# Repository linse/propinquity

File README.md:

Propinquity
===========

Propinquity is a full-body game that is a hybrid between fighting and dancing games. Two players wear proximity sensors on different body parts and as they move to the music, different sensors patches on their bodies light up to indicate when they are active. The players attempt to get as close as possible to active patches on the other player’s body to score points. The longer s(he) can stay “in the sweet spot” (but without actually touching), the higher the resulting score.

[Propinquity on the TAG website](http://playpr.hexagram.ca/projects/?proj=2)

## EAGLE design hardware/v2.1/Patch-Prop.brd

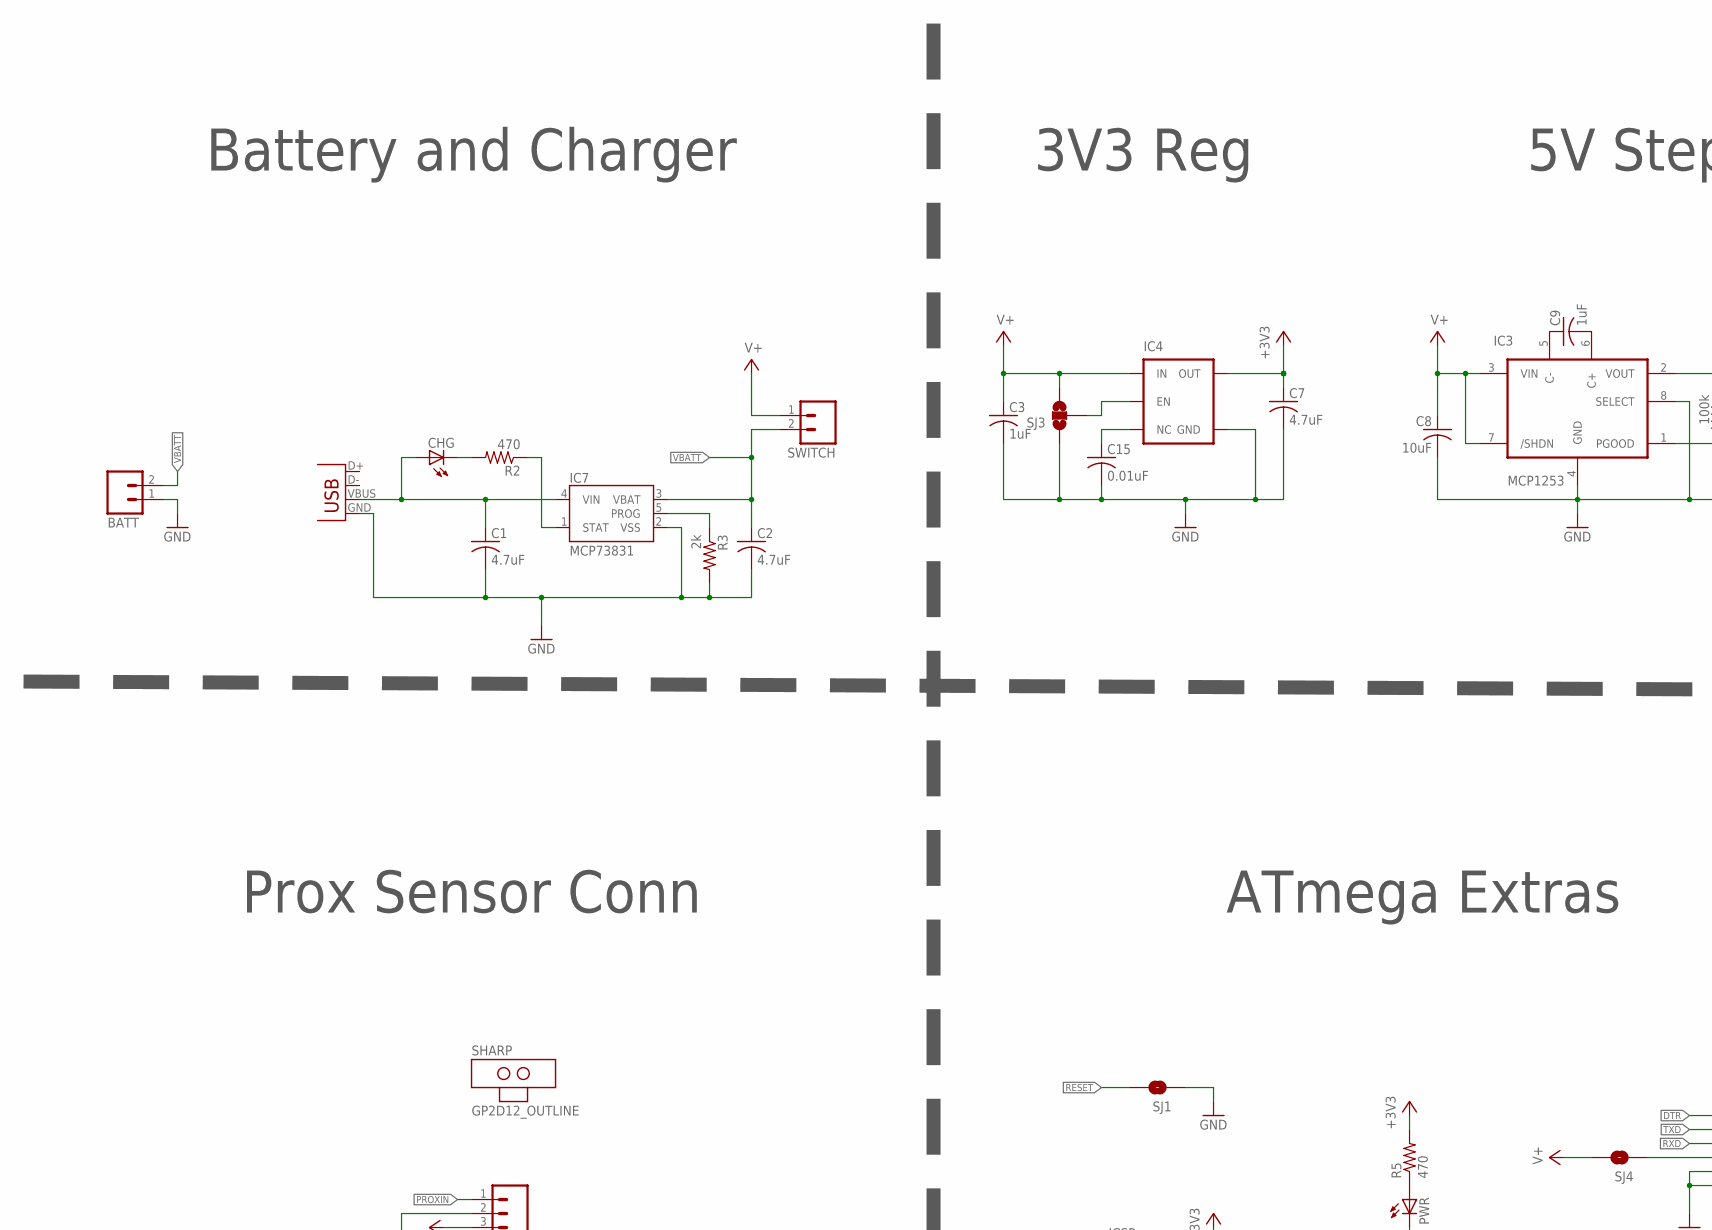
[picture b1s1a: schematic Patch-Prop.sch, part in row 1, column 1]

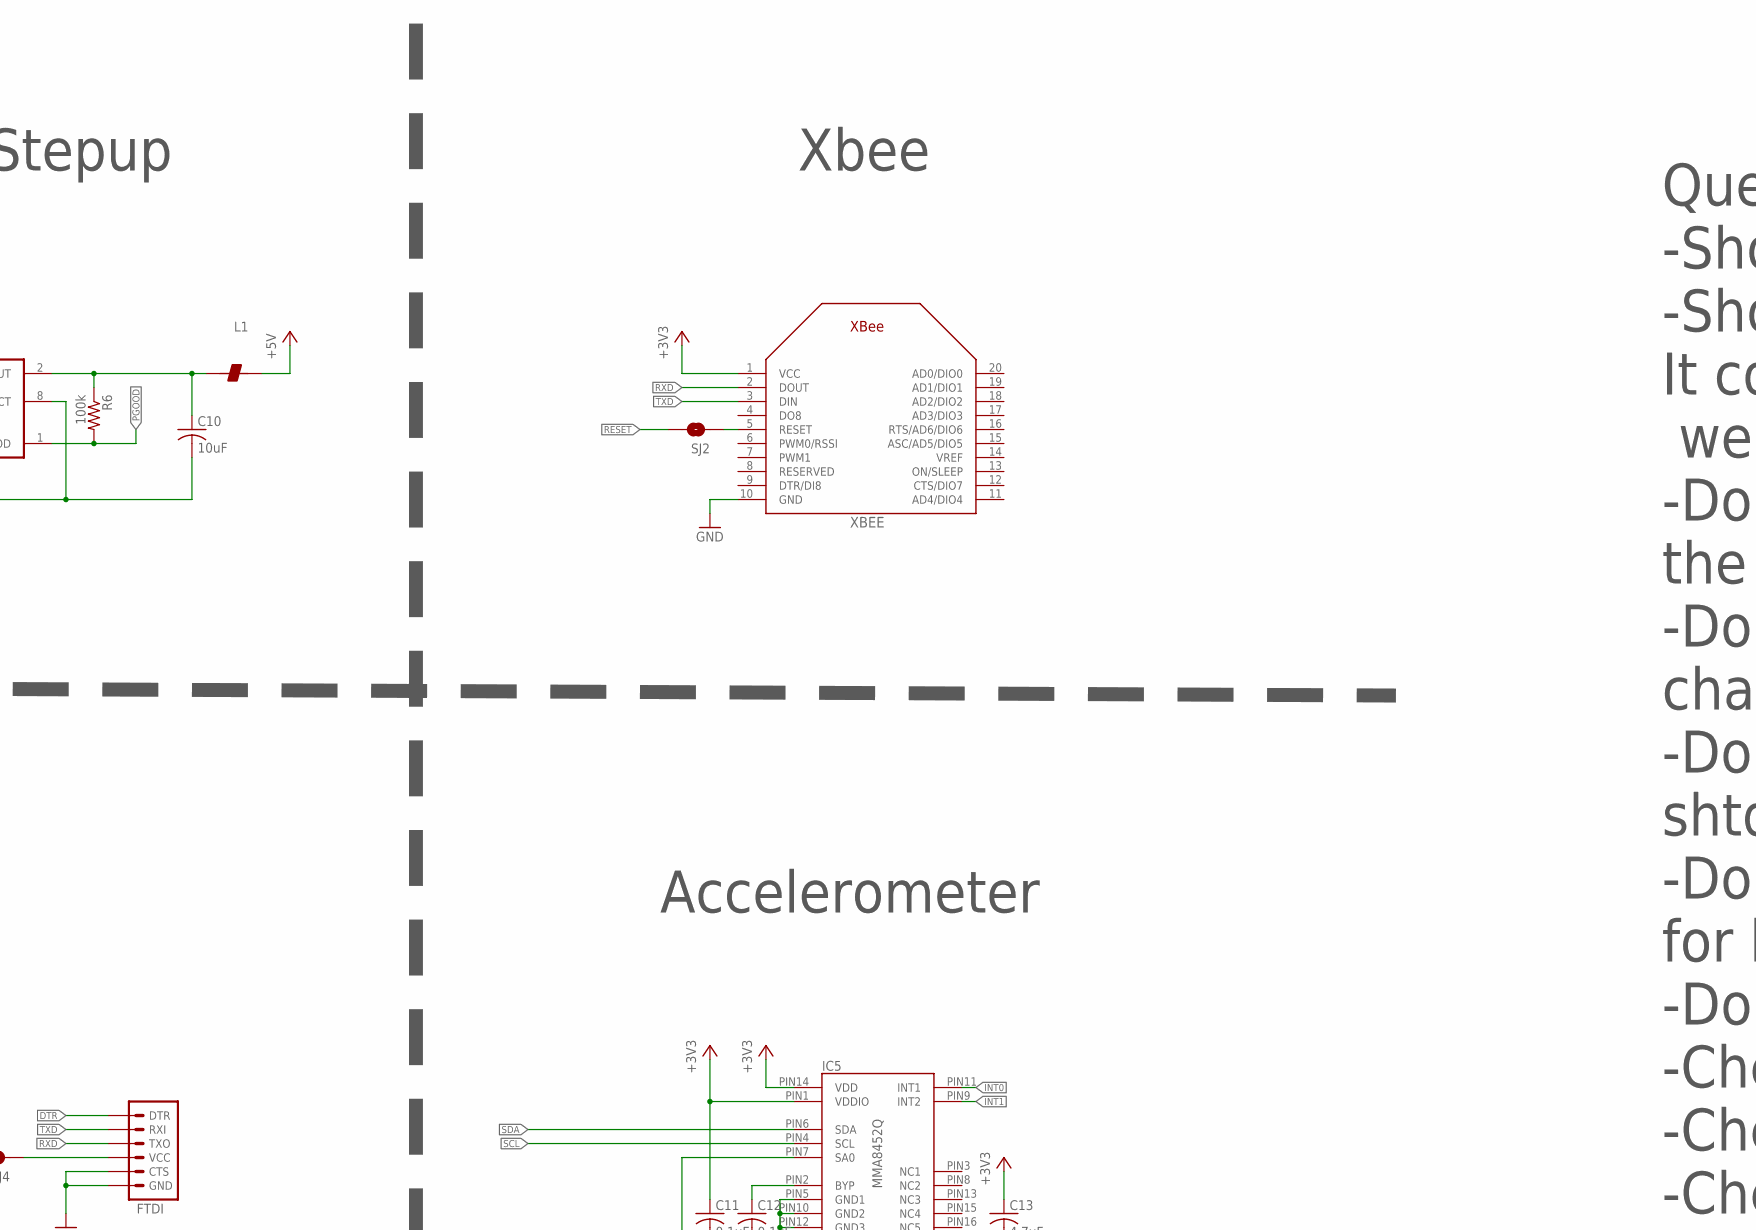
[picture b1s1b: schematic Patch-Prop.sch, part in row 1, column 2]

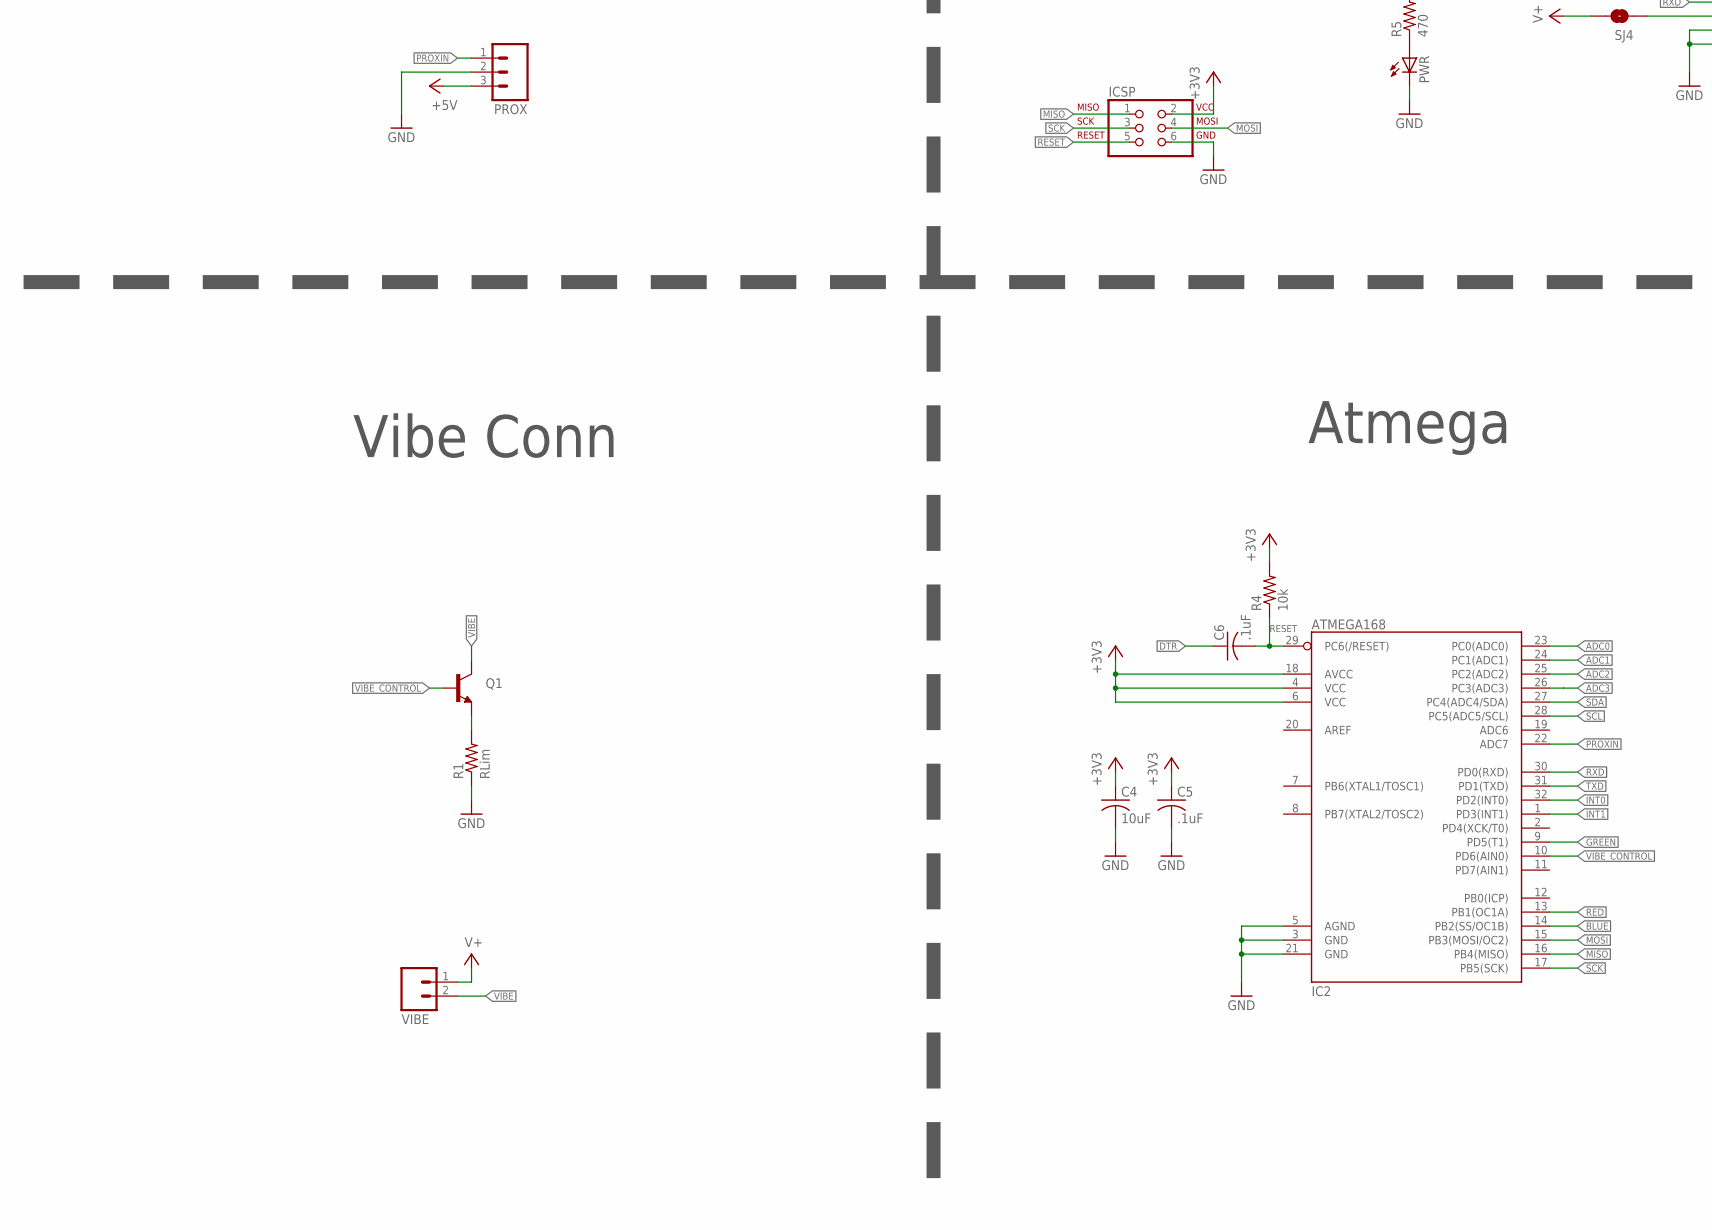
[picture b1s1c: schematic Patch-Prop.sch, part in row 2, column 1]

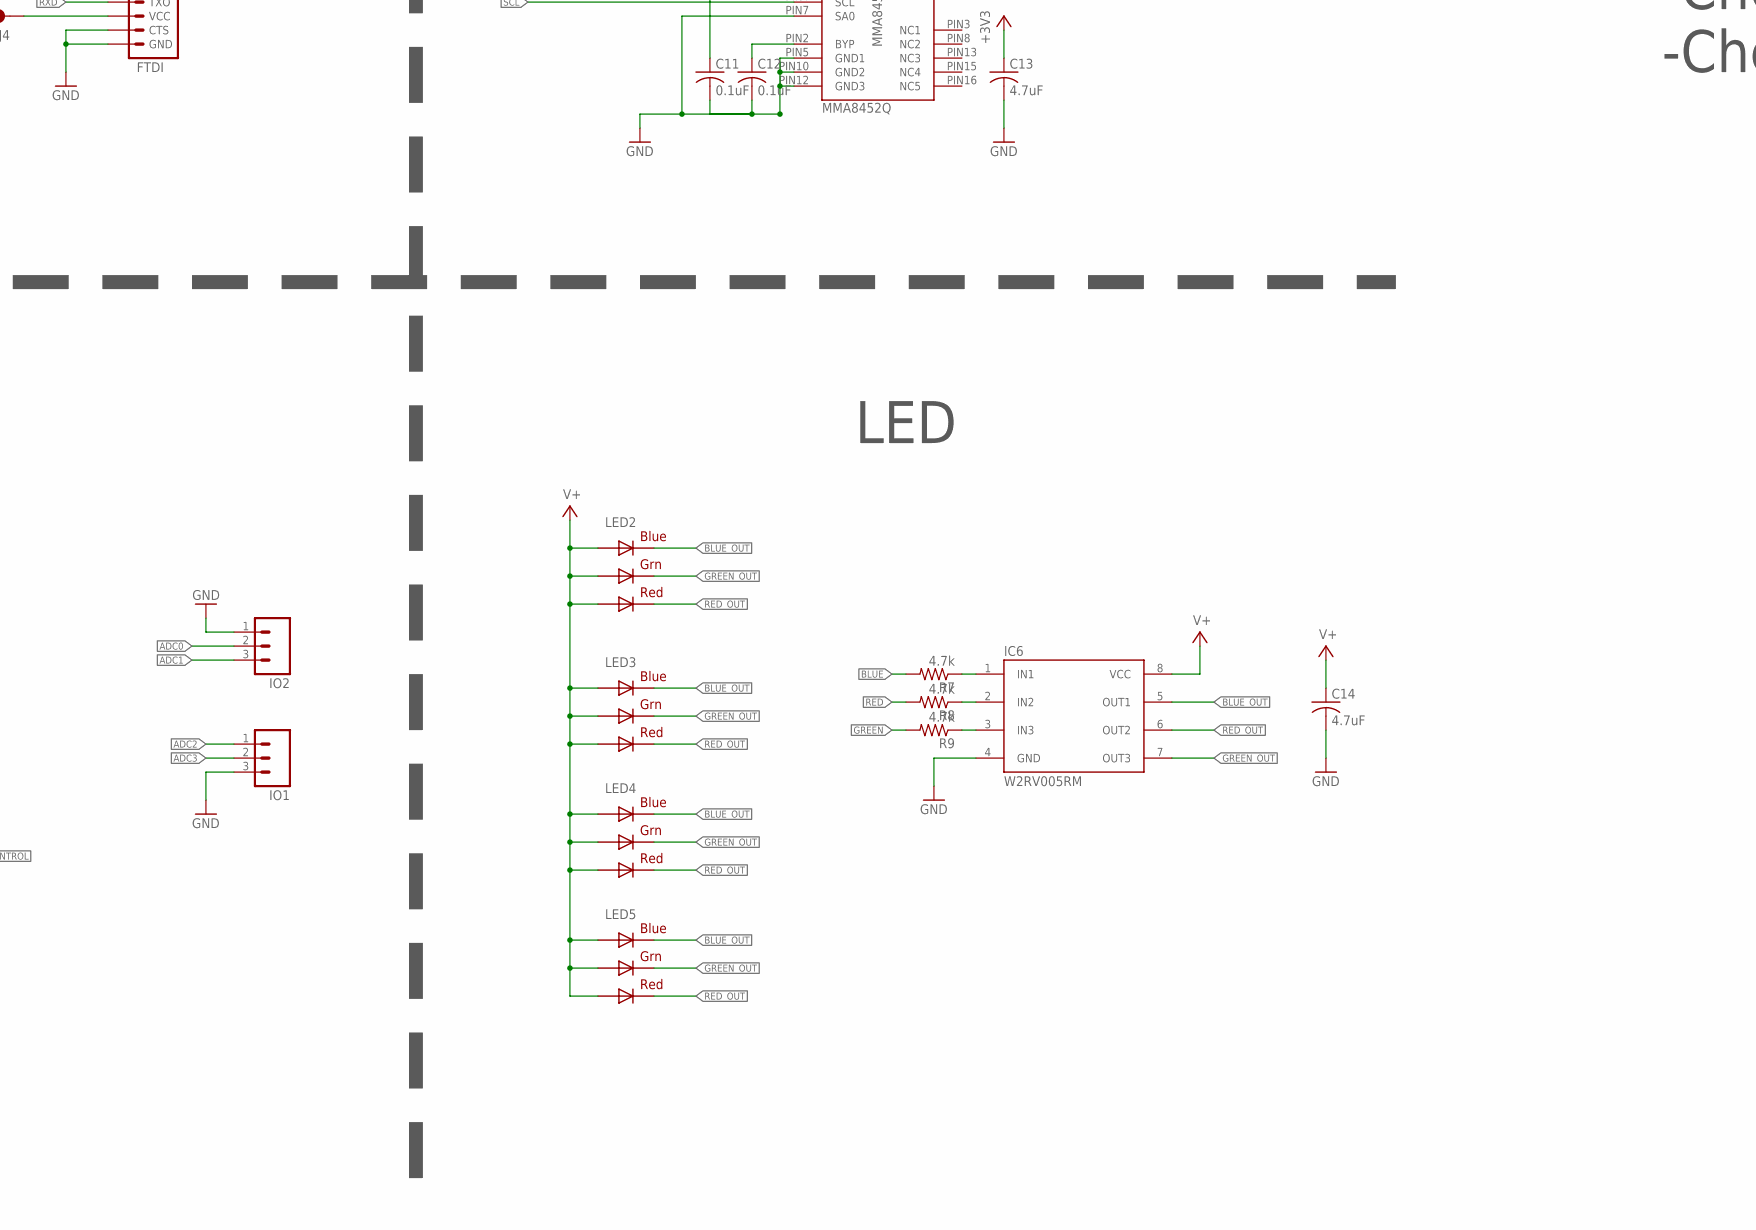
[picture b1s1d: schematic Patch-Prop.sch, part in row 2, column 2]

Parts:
BATT: M02-JST-2MM-SMT; JST-2-SMD
C1, C2, C7, C13, C14: 4.7uF; C0603
C3, C9: 1uF; C0603
C4, C8, C10: 10uF; C0603
C5, C6: .1uF; C0603
C11, C12: 0.1uF; C0603
C15: 0.01uF; C0603
CHG: LEDCHIPLED_0805; CHIPLED_0805
FTDI: ARDUINO_SERIAL_PROGRAMPTH; 1X06
IC2: ATMEGA168; TQFP32-08
IC3: MCP1253; MSOP8
IC4: V_REG_TPS76433SOT23-5; SOT23-5
IC5: MMA8452Q; QFN-16
IC6: W2RV005RM; MSOP8
IC7: MCP73831; SOT23-5
ICSP: ISP-AVR910SMD; 2X03_BORDER
IO1, IO2: M03PTH; 1X03
L1: BEAD-0805; 0805
LED2, LED3, LED4, LED5: RGBLED5050
PROX: M03PTH; 1X03
PWR: LEDCHIPLED_0805; CHIPLED_0805
Q1: TRANSISTOR_NPNSOT23; SOT23
R1: RLim; R0603
R2, R5: 470; R0603
R3: 2k; R0603
R4: 10k; R0603
R6: 100k; R0603
R7, R8, R9: 4.7k; R0603
SHARP: GP2D12_OUTLINE
SJ1, SJ2, SJ4: SOLDERJUMPERNO; SJ_2S-NO
SJ3: SOLDERJUMPER_2WAYS; SJ_3
SWITCH: M02PTH; 1X02
USB: USBSMD; USB-MINIB
VIBE: M02PTH; 1X02
XBEE: XBEE

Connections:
+3V3: C4.1, C5.1, C7.1, C11.1, C13.1, IC2.4 (VCC), IC2.6 (VCC), IC2.18 (AVCC), IC4.5 (OUT), IC5.PIN1 (VDDIO), IC5.PIN14 (VDD), ICSP.2, R4.2, R5.2, XBEE.1 (VCC)
+5V: L1.2, PROX.3
ADC0: IC2.23 (PC0(ADC0)), IO2.2
ADC1: IC2.24 (PC1(ADC1)), IO2.3
ADC2: IC2.25 (PC2(ADC2)), IO1.1
ADC3: IC2.26 (PC3(ADC3)), IO1.2
BLUE: IC2.14 (PB2(SS/OC1B)), R7.2
BLUE_OUT: IC6.5 (OUT1), LED2.4 (BLUE_C), LED3.4 (BLUE_C), LED4.4 (BLUE_C), LED5.4 (BLUE_C)
DTR: C6.1, FTDI.1 (DTR)
GND: BATT.1 (2), C1.2, C2.2, C3.2, C4.2, C5.2, C7.2, C8.2, C10.2, C11.2, C12.2, C13.2, C14.2, C15.2, FTDI.5 (CTS), FTDI.6 (GND), IC2.3 (GND), IC2.5 (AGND), IC2.21 (GND), IC3.4 (GND), IC3.8 (SELECT), IC4.2 (GND), IC5.PIN5 (GND1), IC5.PIN7 (SA0), IC5.PIN10 (GND2), IC5.PIN12 (GND3), IC6.4 (GND), IC7.2 (VSS), ICSP.6, IO1.3, IO2.1, PROX.2, PWR.C, R1.1, R3.2, SJ1.1, SJ3.1, USB.GND, XBEE.10 (GND)
GREEN: IC2.9 (PD5(T1)), R9.2
GREEN_OUT: IC6.7 (OUT3), LED2.6 (GREEN_C), LED3.6 (GREEN_C), LED4.6 (GREEN_C), LED5.6 (GREEN_C)
INT0: IC2.32 (PD2(INT0)), IC5.PIN11 (INT1)
INT1: IC2.1 (PD3(INT1)), IC5.PIN9 (INT2)
MISO: IC2.16 (PB4(MISO)), ICSP.1
MOSI: IC2.15 (PB3(MOSI/OC2)), ICSP.4
unnamed: C15.1, IC4.4 (NC)
unnamed: IC4.3 (EN), SJ3.2
unnamed: C9.1, IC3.5 (C-)
unnamed: Q1.2 (E), R1.2
unnamed: PWR.A, R5.1
unnamed: C9.2, IC3.6 (C+)
unnamed: IC6.1 (IN1), R7.1
unnamed: CHG.C, R2.2
unnamed: IC6.2 (IN2), R8.1
unnamed: C10.1, IC3.2 (VOUT), L1.1, R6.1
unnamed: IC7.5 (PROG), R3.1
unnamed: IC6.3 (IN3), R9.1
unnamed: FTDI.4 (VCC), SJ4.1
unnamed: IC7.1 (STAT), R2.1
unnamed: C12.1, IC5.PIN2 (BYP)
unnamed: SJ2.1, XBEE.5 (RESET)
PGOOD: IC3.1 (PGOOD), R6.2
PROXIN: IC2.22 (ADC7), PROX.1
RED: IC2.13 (PB1(OC1A)), R8.2
RED_OUT: IC6.6 (OUT2), LED2.5 (RED_C), LED3.5 (RED_C), LED4.5 (RED_C), LED5.5 (RED_C)
RESET: C6.2, IC2.29 (PC6(/RESET)), ICSP.5, R4.1, SJ1.2, SJ2.2
RXD: FTDI.3 (TXO), IC2.30 (PD0(RXD)), XBEE.2 (DOUT)
SCK: IC2.17 (PB5(SCK)), ICSP.3
SCL: IC2.28 (PC5(ADC5/SCL)), IC5.PIN4 (SCL)
SDA: IC2.27 (PC4(ADC4/SDA)), IC5.PIN6 (SDA)
TXD: FTDI.2 (RXI), IC2.31 (PD1(TXD)), XBEE.3 (DIN)
USB_VIN: C1.1, CHG.A, IC7.4 (VIN), USB.VBUS
V+: C3.1, C8.1, C14.1, IC3.3 (VIN), IC3.7 (/SHDN), IC4.1 (IN), IC6.8 (VCC), LED2.1 (GREEN_A), LED2.2 (RED_A), LED2.3 (BLUE_A), LED3.1 (GREEN_A), LED3.2 (RED_A), LED3.3 (BLUE_A), LED4.1 (GREEN_A), LED4.2 (RED_A), LED4.3 (BLUE_A), LED5.1 (GREEN_A), LED5.2 (RED_A), LED5.3 (BLUE_A), SJ3.3, SJ4.2, SWITCH.1, VIBE.1
VBATT: BATT.2 (1), C2.1, IC7.3 (VBAT), SWITCH.2
VIBE: Q1.3 (C), VIBE.2
VIBE_CONTROL: IC2.10 (PD6(AIN0)), Q1.1 (B)

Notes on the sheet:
Battery and Charger
3V3 Reg
5V Stepup
Xbee
Accelerometer
ATmega Extras
Prox Sensor Conn
Vibe Conn
Atmega
LED
Questions: -Should the vibe have a connector? -Should the prox have a connector? It could just have header holes and we solder a cable with a connector -Do we want to use the shtdwn for the stepup or power good -Double check we are on PWM channels -Double check stepup select and shtdwn -Double chec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

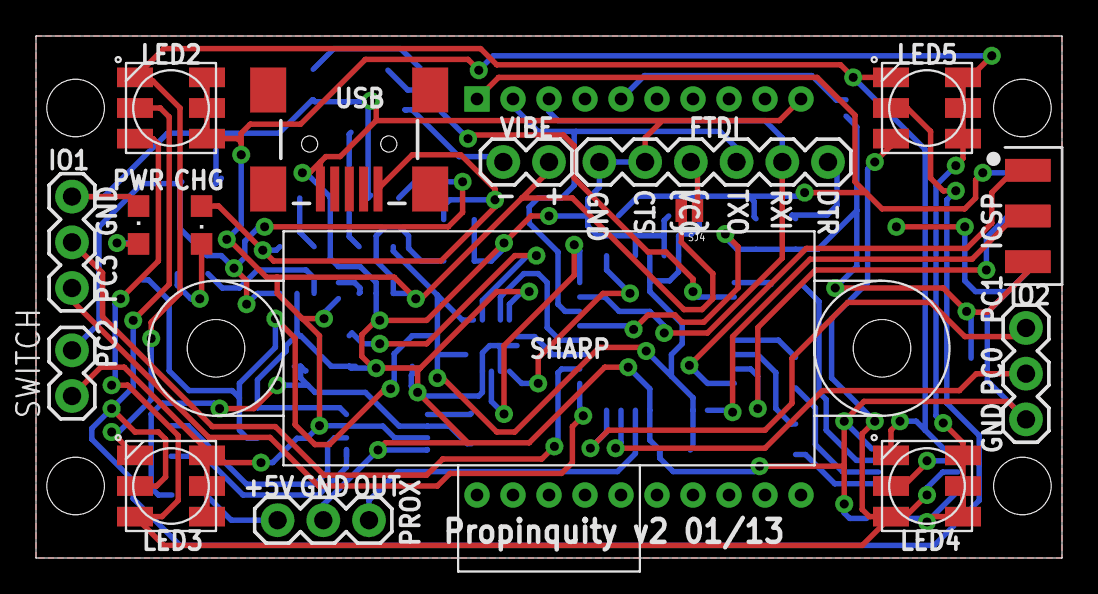
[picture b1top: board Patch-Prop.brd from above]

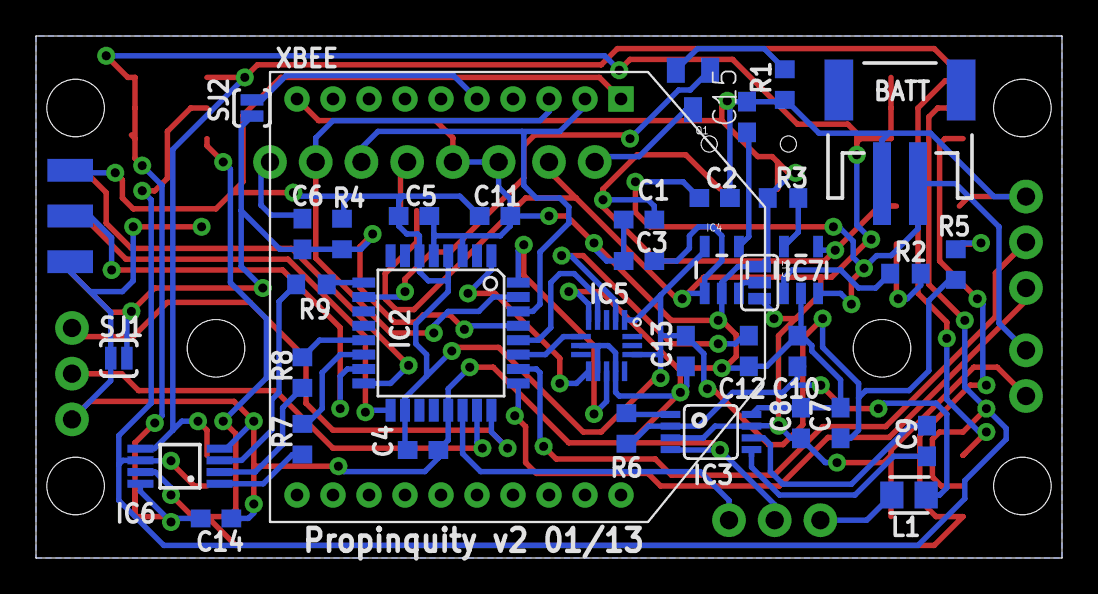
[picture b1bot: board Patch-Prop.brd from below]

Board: 2 copper layers, 57.0 x 29.0 mm, 53 parts (37 on the bottom side), 47 nets.

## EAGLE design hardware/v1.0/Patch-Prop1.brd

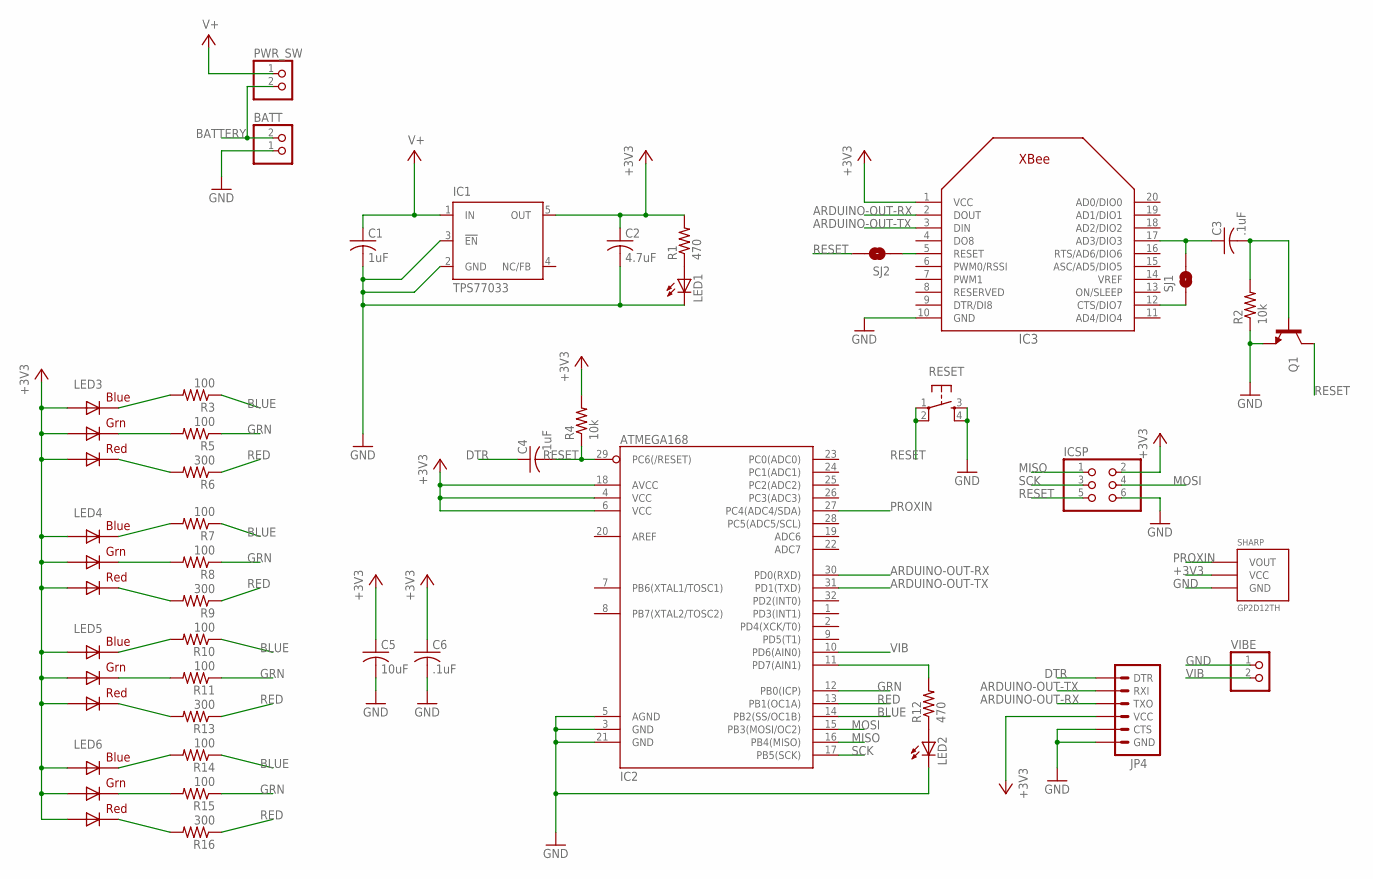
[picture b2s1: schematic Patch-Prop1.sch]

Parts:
BATT: JST_2PIN-SMT-RA; JST-PH-2-SMT-RA
C1: 1uF; C0603
C2: 4.7uF; C0603
C3, C4, C6: .1uF; C0603
C5: 10uF; C0603
IC1: TPS77033; SOT23-DBV
IC2: ATMEGA168; TQFP32-08
IC3: XBEE
ICSP: PINHD-2X3; 2X03
JP4: ARDUINO_SERIAL_PROGRAMSMD; 1X06-SMD
LED1, LED2: LEDCHIPLED_0805; CHIPLED_0805
LED3, LED4, LED5, LED6: RGBLED5050
PWR_SW: PINHD-1X2; 1X02
Q1: TRANSISTOR_NPNSOT89; SOT89
R1, R12: 470; R0603
R2, R4: 10k; R0603
R3, R5, R7, R8, R10, R11, R14, R15: 100; R0603
R6, R9, R13, R16: 300; R0603
RESET: TAC_SWITCHPTH; TACTILE-PTH
SHARP: GP2D12TH; GP2D12
SJ1, SJ2: SOLDERJUMPERNO; SJ_2S-NO
VIBE: PINHD-1X2; 1X02

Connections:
+3V3: C2.1, C5.1, C6.1, IC1.5 (OUT), IC2.4 (VCC), IC2.6 (VCC), IC2.18 (AVCC), IC3.1 (VCC), ICSP.2, JP4.4 (VCC), LED3.1 (GREEN_A), LED3.2 (RED_A), LED3.3 (BLUE_A), LED4.1 (GREEN_A), LED4.2 (RED_A), LED4.3 (BLUE_A), LED5.1 (GREEN_A), LED5.2 (RED_A), LED5.3 (BLUE_A), LED6.1 (GREEN_A), LED6.2 (RED_A), LED6.3 (BLUE_A), R1.2, R4.2, SHARP.VCC
ARDUINO-OUT-RX: IC2.30 (PD0(RXD)), IC3.2 (DOUT), JP4.3 (TXO)
ARDUINO-OUT-TX: IC2.31 (PD1(TXD)), IC3.3 (DIN), JP4.2 (RXI)
BATTERY: BATT.2 (1), PWR_SW.2
BLUE: IC2.14 (PB2(SS/OC1B)), R3.1, R7.1, R10.1, R14.1
DTR: C4.1, JP4.1 (DTR)
GND: BATT.1 (2), C1.2, C2.2, C5.2, C6.2, IC1.2 (GND), IC1.3 (!EN), IC2.3 (GND), IC2.5 (AGND), IC2.21 (GND), IC3.10 (GND), ICSP.6, JP4.5 (CTS), JP4.6 (GND), LED1.C, LED2.C, Q1.3 (E), R2.1, RESET.3, RESET.4, SHARP.GND, VIBE.1
GRN: IC2.12 (PB0(ICP)), R5.1, R8.1, R11.1, R15.1
MISO: IC2.16 (PB4(MISO)), ICSP.1
MOSI: IC2.15 (PB3(MOSI/OC2)), ICSP.4
unnamed: C3.1, IC3.17 (AD3/DIO3), SJ1.2
unnamed: C3.2, Q1.1 (B), R2.2
unnamed: LED1.A, R1.1
unnamed: LED2.A, R12.1
unnamed: IC2.11 (PD7(AIN1)), R12.2
unnamed: LED4.4 (BLUE_C), R7.2
unnamed: LED3.5 (RED_C), R6.2
unnamed: LED3.4 (BLUE_C), R3.2
unnamed: LED3.6 (GREEN_C), R5.2
unnamed: LED4.6 (GREEN_C), R8.2
unnamed: LED5.4 (BLUE_C), R10.2
unnamed: LED4.5 (RED_C), R9.2
unnamed: LED5.5 (RED_C), R13.2
unnamed: LED5.6 (GREEN_C), R11.2
unnamed: LED6.4 (BLUE_C), R14.2
unnamed: LED6.6 (GREEN_C), R15.2
unnamed: LED6.5 (RED_C), R16.2
unnamed: IC3.12 (CTS/DIO7), SJ1.1
unnamed: IC3.5 (RESET), SJ2.1
PROXIN: IC2.27 (PC4(ADC4/SDA)), SHARP.VOUT
RED: IC2.13 (PB1(OC1A)), R6.1, R9.1, R13.1, R16.1
RESET: C4.2, IC2.29 (PC6(/RESET)), ICSP.5, Q1.2 (C), R4.1, RESET.1, RESET.2, SJ2.2
SCK: IC2.17 (PB5(SCK)), ICSP.3
V+: C1.1, IC1.1 (IN), PWR_SW.1
VIB: IC2.10 (PD6(AIN0)), VIBE.2

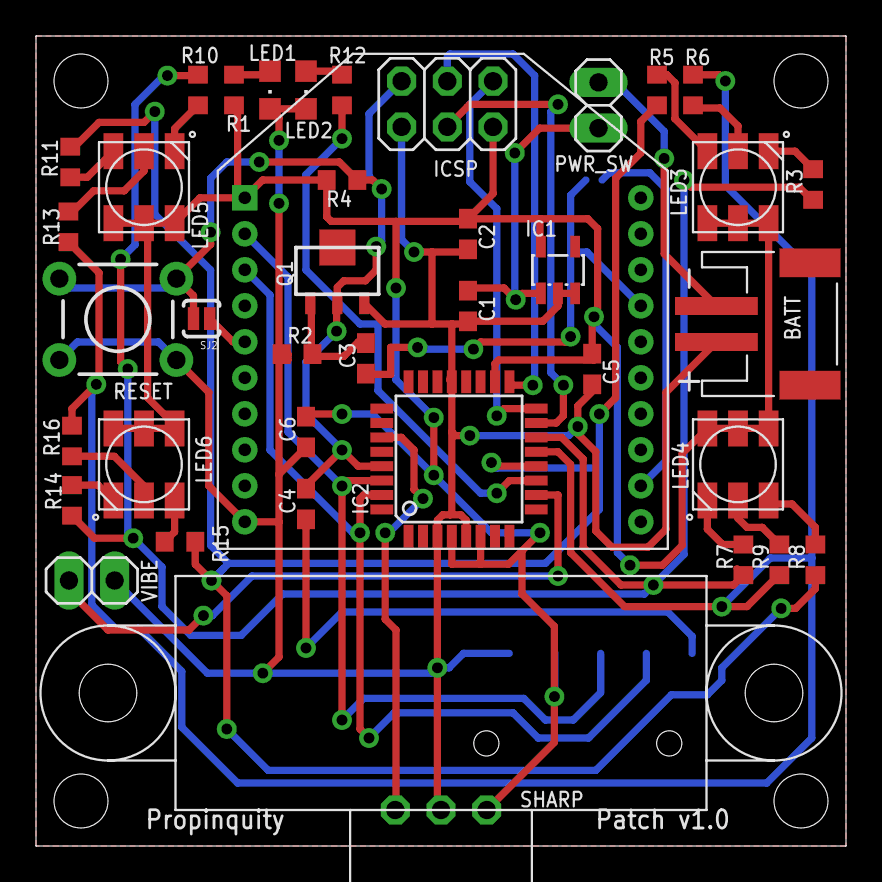
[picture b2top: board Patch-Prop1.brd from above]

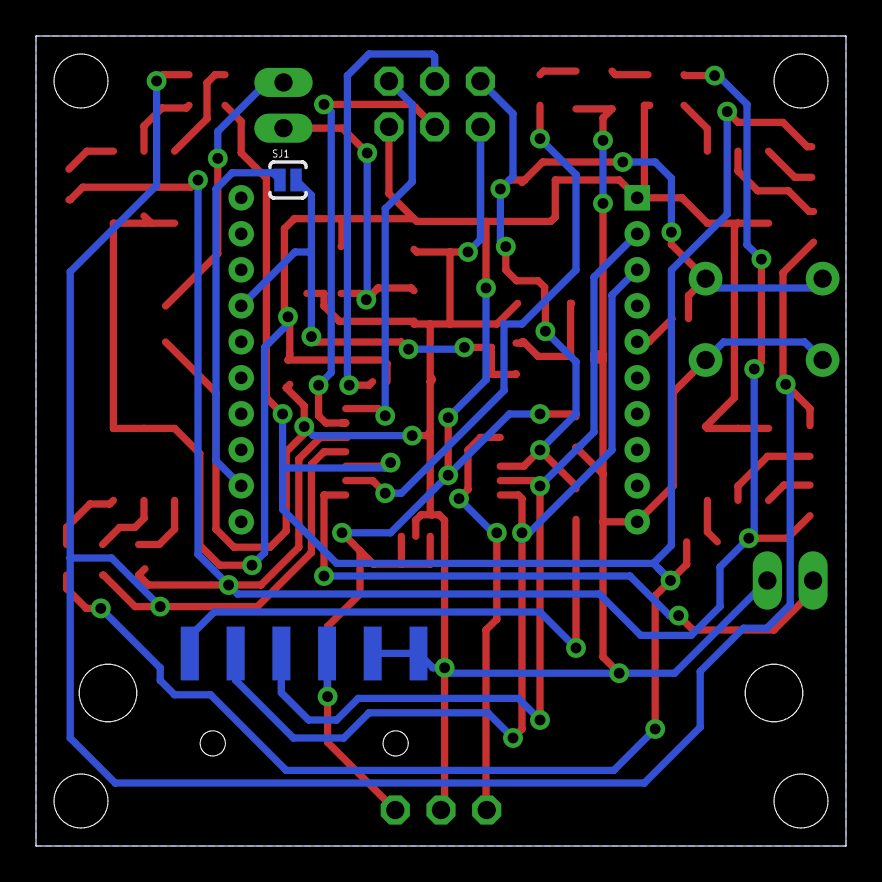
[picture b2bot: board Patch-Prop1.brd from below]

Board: 2 copper layers, 45.0 x 45.0 mm, 41 parts (2 on the bottom side), 35 nets.

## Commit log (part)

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2012-03-08 document new packets
2012-03-09 Cleanups.
2012-03-27 Fixed formatting across all source code. Created a graphics class and refactored artwork handling code into it. Renamed "OutterBoundary" to "OuterBoundary" Changed ignore file to exclude .class files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
2012-03-27 Renamed more files
2012-03-27 Refactorrrrrr
2012-03-27 Awsome native handeling in build.xml
2012-03-27 Cleanup of almost all warnings
2012-03-27 Added project metadata for Eclipse. Minor line break changes.
2012-03-28 Removed player.lst and xbees.lst, and added them to the ignore list, because there's no reason to version them. Moved more content from Propinquity.java to Graphics.java. Changed many ifs for switche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
2012-04-03 Created new class, Sounds.java, to handle everything audio related. Moved all audio code to it accordingly. Also renamed some methods, variables, and removed dead code.
2012-04-04 Correcting some structural issue and standardizing
    Removing unnecessary use of static, avoid as much as possible
    Always prefer passing PApplet over Propinquity for future proofing
    Standardize the naming of the passed PApplet/Propinquity
    Avoid private where not needed
2012-04-04 Added Text.java
2012-04-04 Now using Text to draw arc text; other minor fixes like warnings.
2012-04-05 Added show and hide methods to PlayerList.java and XBeeManager.java so they handle their own drawing. No longer need those funky null checks now... Also shuffled some methods around.
2012-04-05 Keyboard control now uses the new stateChange mechanism
    Implemented support for the the stateChange mechanism in keypress
    This also revealed some other bugs that have been fixed.
2012-04-30 Added main patch firmware branch
2012-04-30 Cleaned up the Level constructors, and got rid of the pointless init()
2012-04-30 Removed initLevel() and moved its contents into the level class.
2012-04-30 Fixed the merge
2012-04-30 Massive movement of all liquid related things from main to a more aptly named class.
2012-04-30 fixing garbage left from previous merge
2012-04-30 Moving more xbee files around
2012-05-01 Working arduino patch firmware base
2012-05-02 Debug UI working
2012-05-02 working with millis based timer
2012-05-02 Corrected build errors
2012-05-02 duty cycle/period on vibe and LEDs working, but dynamically changing values not so much
2012-05-03 Added tentative test of xbee-api
2012-05-05 Added a Colour class to simplify the handling of, well, colours. Other minor fixes in main.
2012-05-06 Fixed up the last of those nullcheck instantiations. Other minor housekeeping.
2012-05-07 *whistles*
2012-05-07 UPERCAAAASSSEE
2012-05-07 Commented out some dead code, down with the warnings.
2012-05-07 Little error
2012-05-07 Working on implementation of XBee
2012-05-07 Formatting work for prettiness.
2012-05-07 Clearing up the liquid and the particles, currently not drawing.
2012-05-07 More wrangling of Level.java into proper shape.
2012-05-07 Implementation of the XBee hardware interface
    Tweaks to HardwareInterface and ProxEventListener
    Proper implementation of the XBee handling in XBeeBaseStation. This
    includes send/receive. Sending is done via the sendPacket() method.
    Recieve updates relevant Patch/Glove objects and notifies
    ProxEventListener listeners.
2012-05-07 Reorganized Debugger controls
    Now scales up to 6 patches legibly
2012-05-08 Operation Liquid2 has begun.
2012-05-08 Small tweaks, working on XBee reliability
    Trying to indentfy reasons for packet loss, playing around with the ACK
2012-05-08 Higher arduino baud rate
2012-05-08 Added basic pieces of gravity, score, physics, and, as usual, still cleaning stuff out.
2012-05-08 Implementation of HardwareSimulator
    Implemented a basic HardwareSimulator and a HardwareSimTest class to
    test it.
    Also a small typo in ProxEventListener
    Added a build target for the new HardwareSimTest main
2012-05-08 Added the shiny new hardware simulator, and finished the basic event listener and scoring code, particles now being created on proxEvents. Also a small improvement to Colour.java.
2012-05-08 Added active to glove + javadocs
    Adding some javadocs
    Added active field for glove
2012-05-08 Now comes with awesome opposite gravities.
2012-05-09 OCD styling
    if/switch/catch other spacing stuff changed
2012-05-09 Tweaky Tweaky
2012-05-09 Made the particles smaller and less blurry, adjusted gravity force accordingly, and fixed some funky eclipse build path settings.
2012-05-09 Adjusted the size of particles used in level/player selection so they aren't tiny.
2012-05-09 Started working on metaball effect.
2012-05-09 Cleanup
2012-05-09 Refactoring LevelSelect
2012-05-10 Clean refactor and reduce
    if/switch/case spaces
    cleanup continues in LevelSelect
2012-05-13 Building automated player instatiation
    Players are now being instantiated after the PlayerList dialog.
    The players are only ever going to be created there. This player list is
    then going to be passed to LevelSelect where player colors can be
    modified from the default and then the player objects are passed to the
    Level objects as they are instantiated
2012-05-13 HUD cleanup working, levelselect almost clean
    Just need to fix level loading mechanism, otherwise levelselect is in
    good shape.
    Started a good job of centralizing the HUD, got rid of the Graphics
    class
2012-05-14 ack mechanism... unfinished
2012-05-14 Updated the fence/boundary artwork, and shifted text and banners accordingly.
2012-05-14 Replacing old hud draw with nicer, more OO banners.
2012-05-14 Banners now draw properly.
2012-05-14 Deleting old hud stuff no longer used.
2012-05-14 Canabilized Player try to merge now
2012-05-14 Refactoring Level elements in Propinquity to Level
2012-05-14 Working revision, added a TODO
    Added a TODO file with more esoteric issues that need to be worked on
    Level is now a UIElement and mostly handles it's own drawing. Still
    maybe no perfect but getting there. Revelant changes were made to
    Propinquity.
    Fixed some syntax issues (Fences, Score)
    Removed all privates (private is evil)
2012-05-14 Removed the last of the old code
2012-05-15 for glove test
2012-05-15 Moving around Level instantiation + gl cleanup
2012-05-16 Split LevelSelect into LevelSelect + PlayerSelect
    Since there were actually two different mechanisms I seperated them into
    two classes.
    Made relevant changes in Propinquity and GameState with the addition of
    a new overall state called PlayerSelect
2012-05-16 Nit pick nit pick
2012-05-16 Particles now merge when their count gets too high. Also fixed some warnings.
2012-05-16 Added some TODOs and made heap bigger in ant build file
2012-05-16 Working on game mechanic and fixing bugs
    Good working PlayerSelect hardware control
    Fixed a bunch of nullpointer or similar bugs in HardwareSimulator
    Tweaks to UIElement and friends
2012-05-16 TODO Cleanup and fixed pause behavior
    Periods now respect pauseing
    Cleaned up todos
2012-05-17 Patch adjusted to return 0 when active is false
2012-05-17 Added README
2012-05-17 Tentativly made hardware control
    Now with hardware control. Seems to disconnect a lot.
    Also exponential scoring
2012-05-18 Somewhat hack build but functional
    Update TODO to reflect findings
    Serious issues with minimal packet sending as there is order loss or
    packet loss resulting in essentially arbitray behavior. Currently I have
    removed all the mechanism that prevent resending when the "new" value is
    equal to the "old" value. Thus if you set the level to 255 when it is
    already 255 it will resend nevertheless. This leads to huge amounts of
2012-05-18 TODOs
2012-05-18 Waviness yay. Needs a fix.
2012-05-23 Tweaks to patch and glove firmware
    Just a little cleanup, keeping the protocol standard
2012-05-23 Various fixes
    Tweaks to patch and glove firmware.
    Just a little cleanup, keeping the protocol standard
    Fixed a little typo
    Removed negative code from player
    Javadoc warning fix
2012-05-23 Logger angst
2012-05-23 Added bubble sounds
2012-05-23 typo
2012-05-23 Cleanup of Level.java
2012-05-23 Implemented most of the HealthLevel logic, and fixed a few warnings.
2012-05-24 Making the build build
    Currently working on BooperLevel and HealthLevel. Neither are
    functioning yet
2012-05-24 Working health level (sim tested)
    The removing of particles was a nice idea however programatically
    inconvenient. Instead I'm using particles like "bleeding". As your
    health drops there are more and more particles appear of your color.
2012-05-24 More tweaks to the new mechanics
    Added a color change for coop on the patches. Fixed some bug
2012-05-28 Working rough metaballs
    Added shaders
2012-05-28 Minor tweak
2012-05-28 Added TODO
2012-05-30 Working on woosh bubble sound
2012-05-30 Improvements to the offscreen draw
2012-05-31 Playtest tweaks
2012-06-05 TODO refactor
2012-06-12 Cleaning up transition system
    Trying to make something more sensible for the transistions, still needs
    a better way to handle "steps" and songs
2012-06-12 Some more simple todo cleanup
    Cleaned up a little the offscreen mess in particle
2012-06-13 Removed forgotten println
2012-06-13 Working on the javadocs
2012-06-20 Morning test Gaite build
2012-06-20 Hide cursor
2012-06-20 Tweaked Levels
2012-06-26 Removing mp3 from repo. Added relevant README
2012-08-20 Added windowed target for ant build file
2012-08-20 Super hack PlayerSelect color thingy
    Now the colors come on, sorta ..
2012-08-22 Added color background and winner's patch lights up
    The winner's patch should now stay on and blink at the end of the level
    The background now changes color to reflect who is winning.
2012-08-22 Added a disable mechanism for bg color + bug fixes
2012-08-22 Added a bunch of break levels
2012-08-22 Modified so you can suppress player scores
2012-10-25 Added a simple class which can toggle all patches for the playtest
2012-10-25 Various tweaks from the playtest
2013-01-17 Added LED driver in MSOP8 package + raw brd file
2013-01-18 Working on PCB
2013-01-19 Tweaks, still 4 drc errors
2013-01-20 Moved uC now routing LEDs
2013-01-20 Tweaking route style and doing cleanup
2013-01-21 Added project name to tname/bname
2013-01-22 Added a bottom stencil
2013-01-29 Smaller cream layers
2013-02-01 Changed fuses and makefile
    -Brown out level was improperly defined in fuses
    -Made the makefile use env variable for programer
2013-02-03 Working on updated firmware for patch with accel
2013-02-04 Updated patch firmware, complete but untested:
    -Basic support for acceleromter XYZ output
    -Simple remote CONF for accel
    -Some resiliency/error checking in case accel doesn't work
    -General cleanup, better code practices
    -New mode variable allowing to selectively enable/disable periferals
2013-02-04 Some small but fixes after real world testing
2013-02-08 Changed default file state
2013-02-08 Added a throttled send mechanism.
    -Corrected a bug in MIN_PACK which sent large amounts of clear messages
    -Added a throttled mode preventing more than 1 packet per second
2013-02-08 Accel interrupt for patch
2013-02-09 Fixed activation bug
2013-02-09 Hardcode a less sensitive accel threshold
2013-02-09 Orb game one step further
2013-02-09 Added Cult Level
2013-02-09 Working cult level
2013-02-09 Added daemon waveform support
2013-02-09 Orb game one step further. Renamed AccelLevel to OrbLevel
2013-02-09 Firmware for a patch with 3 prox sensors
2013-02-11 Some idea dumps in the todo
2013-02-11 Added some sounds
2013-02-11 Some todos and file location fixes
2013-04-21 Switch for charging topology, added jumper for FTDI, Stepup to V+
    -Added a header for a switch between battery and V+. When the switch is
    off, only the charger IC is still connected to the battery
    -Disconnected FTDI from +3v3 now jumper to V+
    -Now connected setupup to V+ instead of +3v3
2013-04-21 Working on routing, noting progress
2013-04-21 Upped the DRC tolerance to 10mil where possible
2013-04-21 Some TODO changes
2013-04-22 Renaming level files
2013-04-22 Added text for all levels in LevelSelect HUD
    All song names can now be seen in level select HUD for clarity and ease
    of selection
2013-04-22 Added a jump to machanism for skipping
    -Prox level now supports pressing 's' to skip to the next transistion
    -Trying to work out the kinks of the dingding and other audio buffering
    -Adjusting tau/saturation for bg some more
2013-04-23 Added Serializer and added serialization for scaling
    Scaling gets saved in a serialized filed
2013-04-23 Added BPM display in LevelSelect
2013-05-01 Added double clickable launchers
2013-05-01 Some small fixes after talking with jane

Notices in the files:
parts and their libraries:
SparkFun: Licensing: CC v3.0 Share-Alike You are welcome to use this library for commercial purposes.
